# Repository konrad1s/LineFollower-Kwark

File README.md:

## Introduction

The LineFollower Robot is an autonomous robot designed to follow a predefined path marked by a black or white line.<br>
This project serves a quite advanced solution including hardware project, embedded software and PC QT application.

A short video demo is available on [YouTube](https://www.youtube.com/watch?v=Kh0NfI-lTgY).

Example - one of the first - linefollower run:

## Hardware
### **High level block diagram**

[![](https://mermaid.ink/img/pako:eNqVlW1vmzAQx7-K5ddJGiCEBE2T8tB2VWHJIM2kOVXlBjdBAxw59tb04bvPxk0ChLYaL8Bnfvf33dkcz3BJIwJduGJ4swaz4SJbZEBeW3Gvp0Y0TUUWLzGPaQZQybzVrLqGiSCcUr5GhxHwaSQS8gaRLDrRntK_hN2FYrNJdgDlFtBWQdmLp9S568yRGgCn1ZmDIeacsCIUcnwfJ_ETYdadNUdWy5qDOU04XhEQkJVIMKesRhQ0my9K8qXZ_FoReT9sf3QDkLwV9KKYkWVeIS84zk7CkWn7355QfgeT7TJOdCRq3ZF3rZed-ZZ54ZgmOow-qFlIsi2VRdttOUkB0mZtJGozD_XJsS0yzEdwPbsK2o5hhMV6nI_1SzW4PfFT4Q7Go3K4BWo_pbjL6dUkB5XUSR7nmTpwzEOD0G532nsbeOSB35aQoIoE8WpdYTy14A-BI4a5YKQuvr3ax2SlyGMW_yEA5Y9CNXwq9y6flAnMht2uYV58v9R0KYUKHJzCxWQOtIfyR61S8Pau6liq_fSnf3aofzHa_-SD-pyVi45iIvhG8KObV5_3-w7VFbQ2XmVEQ_sNrlahHgtOztmxC32RHjeDYFZ3OEoNSHKqb-gYRzefEKXv8H327NBd8pJ8IlrqrrABU8JSHEeyPz8rzwXka5KSBXTlMMLs9wIuslfJYcFpuMuW0OVMkAZkVKzW0H3AyVZaYhNhTsYxloc73SMbnP2itGhC9xk-QtexW72O_PC6_b7TdtqW0YA76Bq9luUYdsfoO92-2XOM1wZ8yv3brb7V6Rt2z7ZkV-nZpnQgUSw3y9e_lvwP8_oPiOn1SA?type=png)](https://mermaid.live/edit#pako:eNqVlW1vmzAQx7-K5ddJGiCEBE2T8tB2VWHJIM2kOVXlBjdBAxw59tb04bvPxk0ChLYaL8Bnfvf33dkcz3BJIwJduGJ4swaz4SJbZEBeW3Gvp0Y0TUUWLzGPaQZQybzVrLqGiSCcUr5GhxHwaSQS8gaRLDrRntK_hN2FYrNJdgDlFtBWQdmLp9S568yRGgCn1ZmDIeacsCIUcnwfJ_ETYdadNUdWy5qDOU04XhEQkJVIMKesRhQ0my9K8qXZ_FoReT9sf3QDkLwV9KKYkWVeIS84zk7CkWn7355QfgeT7TJOdCRq3ZF3rZed-ZZ54ZgmOow-qFlIsi2VRdttOUkB0mZtJGozD_XJsS0yzEdwPbsK2o5hhMV6nI_1SzW4PfFT4Q7Go3K4BWo_pbjL6dUkB5XUSR7nmTpwzEOD0G532nsbeOSB35aQoIoE8WpdYTy14A-BI4a5YKQuvr3ax2SlyGMW_yEA5Y9CNXwq9y6flAnMht2uYV58v9R0KYUKHJzCxWQOtIfyR61S8Pau6liq_fSnf3aofzHa_-SD-pyVi45iIvhG8KObV5_3-w7VFbQ2XmVEQ_sNrlahHgtOztmxC32RHjeDYFZ3OEoNSHKqb-gYRzefEKXv8H327NBd8pJ8IlrqrrABU8JSHEeyPz8rzwXka5KSBXTlMMLs9wIuslfJYcFpuMuW0OVMkAZkVKzW0H3AyVZaYhNhTsYxloc73SMbnP2itGhC9xk-QtexW72O_PC6_b7TdtqW0YA76Bq9luUYdsfoO92-2XOM1wZ8yv3brb7V6Rt2z7ZkV-nZpnQgUSw3y9e_lvwP8_oPiOn1SA)

### **Schematic and PCB**
Electronic circuit diagrams are available in the [Hardware/release/schematic](Hardware/release/schematic) folder.<br>
Gerbers files are available in the [Hardware/release/gerbers](Hardware/release/gerbers) folder.

**Main board:**

**Sensor board:**

**Encoder board:**

### **Component Details**
1. **STM32F722 MCU** <br>
ARM Cortex M7 microcontroller operating at the 216MHz with FPU, Cache, ITCM, DTCM. It powerful enough to handle algorithms and real-time processing required in linefollower applications.
3. **12x KTIR0711S** <br>
Phototransistor-based infrared sensors used to detect the line by measuring reflected IR light. Arranged in a array at the front of the robot to detect the position of the line. Outputs are connected to the MCU's ADC channels for monitoring.
4. **12x LEDs** <br>
Each LED corresponds to a KTIR0711S sensor, turned on when the sensor detects the line.
5. **2x AMS AS5040 Encoders** <br>
10-bit contactless magnetic rotary encoders providing precise angular position measurements. Thanks to the closed-loop control, encoders enables precise control of motor by providing feedback (velocity) for PID controllers.
6. **2x Pololu TB6612FNG Motor Driver Modules** <br>
H-bridge motor driver modules capable of controlling DC motors. Controller channels are combined to obtain higher current capacity.
7. **2x Pololu Motor 10:1 HPCB 6V DC Motors** <br>
High-power micro metal gearmotors with a 10:1 gear ratio
8. **Bluetooth Module JDY-31** <br>
Bluetooth serial module enables wireless communication between the robot and PC application.
9. **Power Supply Components** <br>
LiPo 7.4V battery used due to high energy density and ability to deliver powerful burst of current.<br>
3.3V Low dropout voltage regulator - steps down the battery voltage for MCU, sensors and others modules.

## Software

### **Main run loop**

The core functionality is implemented through an event-driven state machine. The primary signal is the LF_SIG_ADC_DATA_UPDATED, which is raised whenever new ADC data is available. Currently every 5ms, however increasing this frequency can lead to better control results.

The activity diagram presents simplified main robot algorithm in RUN state:

### **Code Structure**

Short brief about implemented software components:

- **linefollower:**
The core component of the software, manages the main event driven state machine. It handles the initialization of all subsystems. This component integrates sensor data processing, PID control algorithms, encoder feedback, and motor management. Additionally, it facilitates communication with the PC application for debugging and configuration purposes.
- **linefollower_config:**
Defines the default configurations and settings for the robot. This ensures that all hardware related configurations is easily adjustable.
- **lf_signal_queue:**
Implements a signal queue used for managing events and signals within the state machine.
- **linefollower_commands:**
Handles the processing of serial communication protocol (SCP) commands received from the PC application. It defines a set of commands for controlling the robot's modes, resetting the MCU, initiating calibration, reading and writing NVM data, toggling debug mode, retrieving session information, and entering the bootloader for firmware updates.
- **lf_calibrate:**
Manages the calibration process for the sensors. It handles the collection of sensor data during calibration runs, computes appropriate threshold values based on the collected values.
- **sensors:**
The module is responsible for interfacing with the robot's sensors to detect the line. It processes ADC data to determine states and manages the associated LEDs. Also implements algorithms to detect specific straight lines and right angles.
- **pid:**
Implements the PID control algorithms used to regulate the robot's motor speeds based on sensor and encoder feedback.
- **encoder:**
Manages the interfacing with the motor encoders to track the robot's velocity.
- **tb6612_motor:**
The module interfaces with the TB6612 motor driver hardware to control the robot's motors.
- **nvm:**
The module handles non-volatile memory operations, enabling the storage and retrieval of configuration data, calibration settings, and runtime parameters. The module ensures data integrity through CRC verification. The nvm module allows the robot to retain configurations across power cycles.
- **scp:**
Implements the Serial Communication Protocol (SCP) used for communication between the robot and external interfaces such as the PC application.
- **scp_dispatcher:**
The module acts as a handler for processing SCP commands received via the scp module. It manages a global command queue using a circular buffer to store incoming data, parses SCP packets, verifies data integrity using CRC, and dispatches valid commands to their respective handlers.

## Bootloader
Implemented bootloader allows for over the air firmware updates without the need of programmer. This is particularly useful for making quick updates "on the road." The bootloader uses the implemented SCP (Serial Communication Protocol) to receive firmware updates over Bluetooth.

There are 2 methods to enter the Bootloader:
1. **Command-Based Entry From Application** <br>
Send a specific command to trigger reset to the bootloader.
2. **Backdoor Entry** <br>
Enter the bootloader upon power-up by sending a specific command. Ensures that firmware updates are always possible, even if the application has errors causing continuous resets.

FLASH memory layout:

## **QT Application**

The QT Application provides a graphical interface to control, configure, and monitor the robot. The main sections of the interface and their functionalities are as follows:
1. **Connection Panel** <br>
Connection indicator and buttons to establish or terminate Bluetooth communication.
2. **Control Panel**<br>
Starting, stopping, resetting, and calibrating the robot, along with options to enable debug mode, read/write NVM, and display real-time data (speed, error, and timing metrics).
3. **Sensors Panel**<br>
Real-time sensor data display showing actual values, calibration references, and sensor weights.
4. **Configuration**<br>
Includes settings for general parameters, PID tuning for motor control, and encoder adjustments.
5. **Graph**<br>
A real-time graph displaying motor speeds, speed reduction, sensors error, enabling data analysis and adjustments for optimal performance.
6. **Bootloader**<br>
Firmware update controls, including options to enter bootloader mode, switch to the main application and flash new firmware via Bluetooth.
7. **Logs**<br>
Real-time log display with options to save or clear logs, providing detailed event tracking for debugging.

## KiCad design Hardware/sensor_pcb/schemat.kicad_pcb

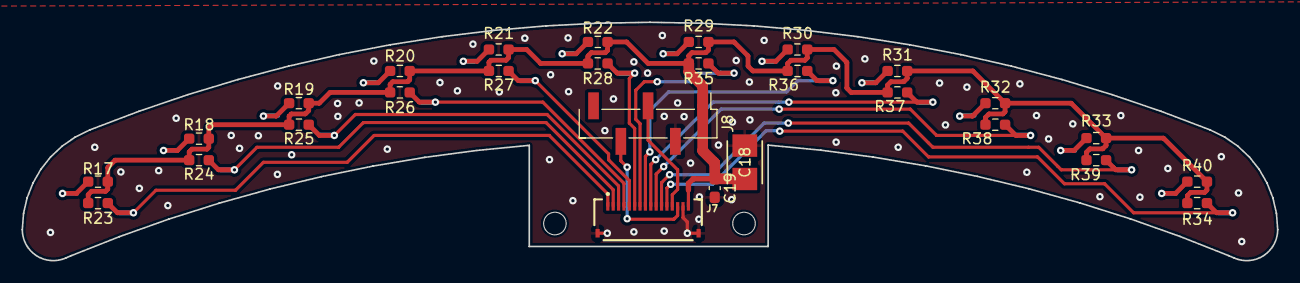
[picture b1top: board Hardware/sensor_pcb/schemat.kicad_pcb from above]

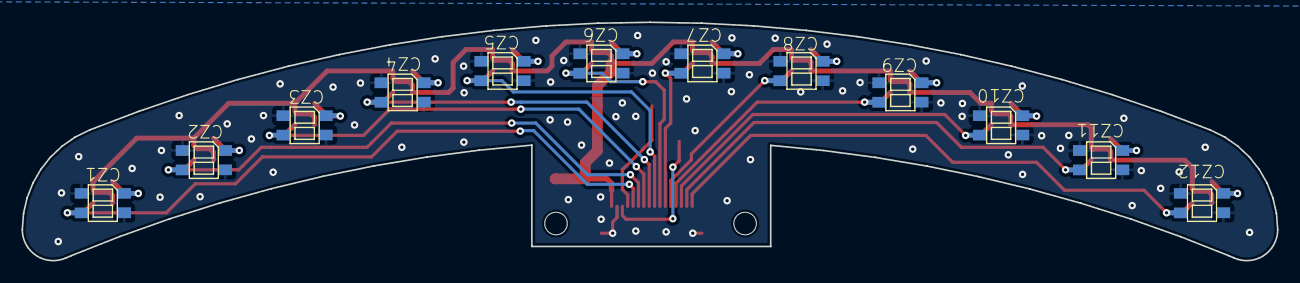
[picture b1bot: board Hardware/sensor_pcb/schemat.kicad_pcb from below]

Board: 2 copper layers, 116.8 x 22.2 mm, 42 parts (12 on the bottom side), 28 nets.

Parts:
@HOLE8, @HOLE9: (no value)
C18: 10uF; CAP_293D-B_VSS
C19: 100nF; C_0603_1608Metric_Pad1.08x0.95mm_HandSolder
CZ1, CZ2, CZ3, CZ4, CZ5, CZ6, CZ7, CZ8, CZ9, CZ10, CZ11, CZ12: KTIR0711S; TOP
J7: SENSOR_CONN; GCT_FFC2B28-16-G
J8: ToF Sensor; PinHeader_1x05_P2.54mm_Vertical_SMD_Pin1Left
R17, R18, R19, R20, R21, R22, R29, R30, R31, R32, R33, R34: 120; R_0603_1608Metric_Pad0.98x0.95mm_HandSolder
R23, R24, R25, R26, R27, R28, R35, R36, R37, R38, R39, R40: 20k; R_0603_1608Metric_Pad0.98x0.95mm_HandSolder

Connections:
+3.3V: C18.1, C19.1, J7.16, J8.1, R17.1, R18.1, R19.1, R20.1, R21.1, R22.1, R23.1, R24.1, R25.1, R26.1, R27.1, R28.1, R29.1, R30.1, R31.1, R32.1, R33.1, R34.1, R35.1, R36.1, R37.1, R38.1, R39.1, R40.1
/schemat_2/I2C_SCL: J7.13, J8.3
/schemat_2/I2C_SDA: J7.14, J8.4
/schemat_2/SENSOR1: CZ12.KOLEKTOR, J7.1, R23.2
/schemat_2/SENSOR2: CZ11.KOLEKTOR, J7.2, R24.2
/schemat_2/SENSOR3: CZ10.KOLEKTOR, J7.3, R25.2
/schemat_2/SENSOR4: CZ9.KOLEKTOR, J7.4, R26.2
/schemat_2/SENSOR5: CZ8.KOLEKTOR, J7.5, R27.2
/schemat_2/SENSOR6: CZ7.KOLEKTOR, J7.6, R28.2
/schemat_2/SENSOR7: CZ6.KOLEKTOR, J7.7, R35.2
/schemat_2/SENSOR8: CZ5.KOLEKTOR, J7.8, R36.2
/schemat_2/SENSOR9: CZ4.KOLEKTOR, J7.9, R37.2
/schemat_2/SENSOR10: CZ3.KOLEKTOR, J7.10, R38.2
/schemat_2/SENSOR11: CZ2.KOLEKTOR, J7.11, R39.2
/schemat_2/SENSOR12: CZ1.KOLEKTOR, J7.12, R40.2
GND: C18.2, C19.2, CZ1.EMITER, CZ1.KATODA, CZ2.EMITER, CZ2.KATODA, CZ3.EMITER, CZ3.KATODA, CZ4.EMITER, CZ4.KATODA, CZ5.EMITER, CZ5.KATODA, CZ6.EMITER, CZ6.KATODA, CZ7.EMITER, CZ7.KATODA, CZ8.EMITER, CZ8.KATODA, CZ9.EMITER, CZ9.KATODA, CZ10.EMITER, CZ10.KATODA, CZ11.EMITER, CZ11.KATODA, CZ12.EMITER, CZ12.KATODA, J7.15, J7.S1 (SHIELD), J7.S2 (SHIELD), J8.2
unnamed: CZ1.ANODA, R34.2
unnamed: CZ2.ANODA, R33.2
unnamed: CZ3.ANODA, R32.2
unnamed: CZ4.ANODA, R31.2
unnamed: CZ5.ANODA, R30.2
unnamed: CZ6.ANODA, R29.2
unnamed: CZ7.ANODA, R22.2
unnamed: CZ8.ANODA, R21.2
unnamed: CZ9.ANODA, R20.2
unnamed: CZ10.ANODA, R19.2
unnamed: CZ11.ANODA, R18.2
unnamed: CZ12.ANODA, R17.2

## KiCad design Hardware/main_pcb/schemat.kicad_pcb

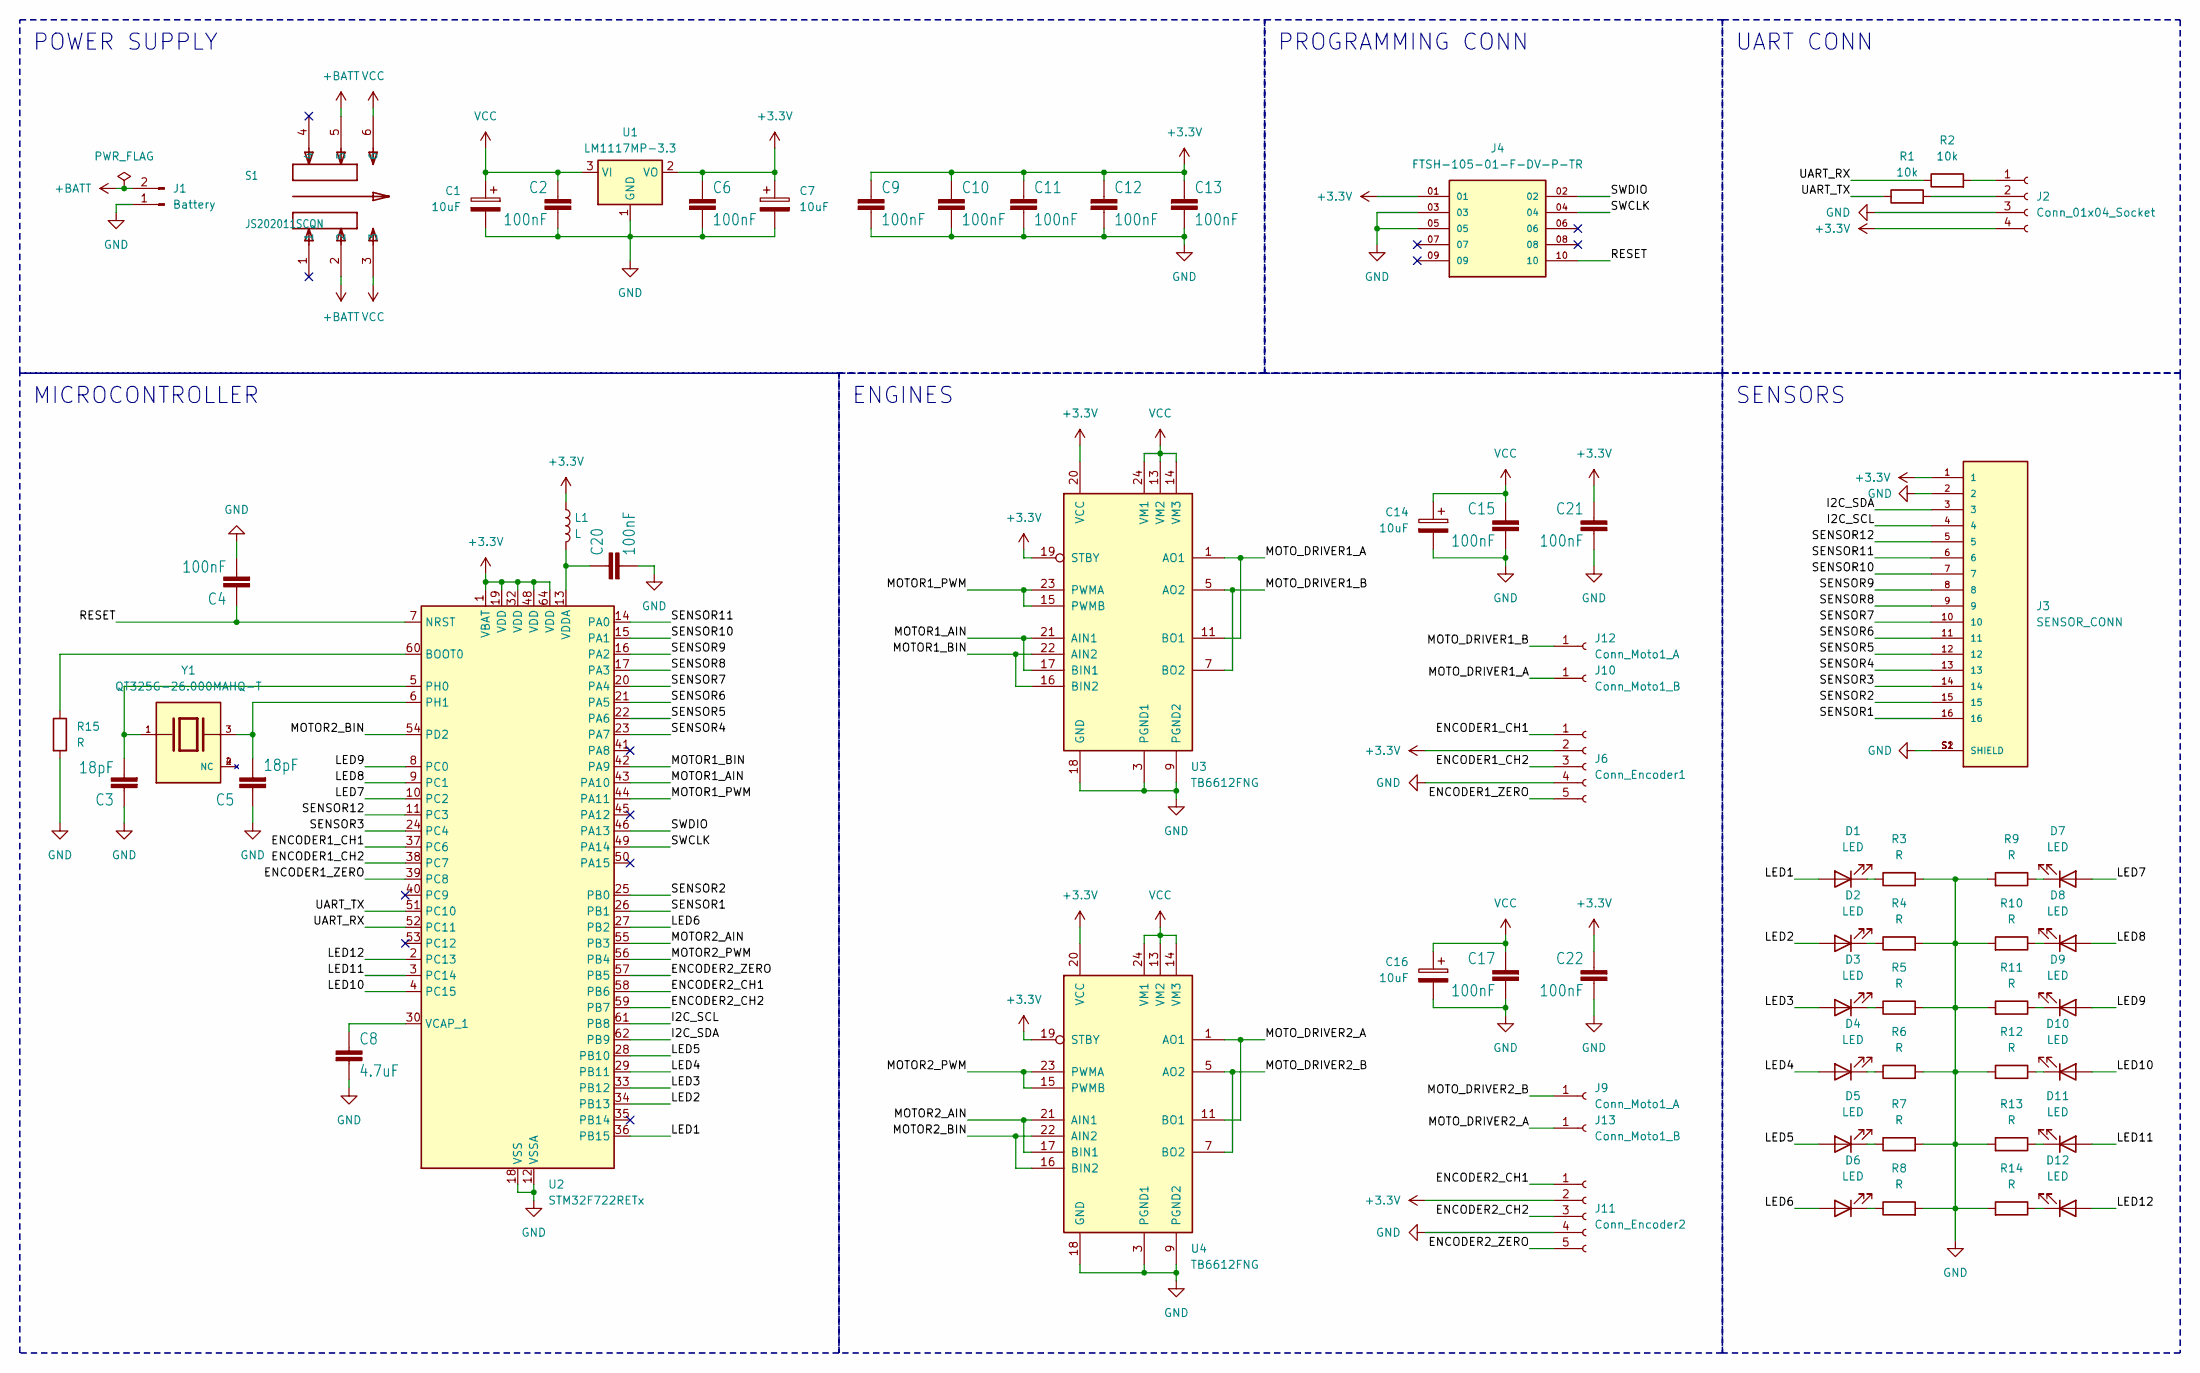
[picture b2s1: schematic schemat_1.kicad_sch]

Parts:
C1, C7, C14, C16: 10uF; CAP_293D-B_VSS
C2, C4, C6, C9, C10, C11, C12, C13, C15, C17, C20, C21, C22: 100nF; C_0603_1608Metric_Pad1.08x0.95mm_HandSolder
C3, C5: 18pF; C_0603_1608Metric_Pad1.08x0.95mm_HandSolder
C8: 4.7uF; C_0603_1608Metric_Pad1.08x0.95mm_HandSolder
D1, D2, D3, D4, D5, D6, D7, D8, D9, D10, D11, D12: LED; LED_0603_1608Metric_Pad1.05x0.95mm_HandSolder
J1: Battery; PinSocket_1x02_P2.54mm_Vertical
J2: Conn_01x04_Socket; PinSocket_1x04_P2.54mm_Vertical
J3: SENSOR_CONN; GCT_FFC2B28-16-G; PARTREV A
J4: FTSH-105-01-F-DV-P-TR; SAMTEC_FTSH-105-01-F-DV-P-TR; PARTREV R
J6: Conn_Encoder1; PinHeader_2x03_P2.54mm_Vertical_SMD
J9, J12: Conn_Moto1_A; PinHeader_1x01_P2.54mm_Vertical
J10, J13: Conn_Moto1_B; PinHeader_1x01_P2.54mm_Vertical
J11: Conn_Encoder2; PinHeader_2x03_P2.54mm_Vertical_SMD
L1: L; L_0603_1608Metric_Pad1.05x0.95mm_HandSolder
R1, R2: 10k; R_0603_1608Metric_Pad0.98x0.95mm_HandSolder
R3, R4, R5, R6, R7, R8, R9, R10, R11, R12, R13, R14, R15: R; R_0603_1608Metric_Pad0.98x0.95mm_HandSolder
S1: JS202011SCQN; SW_JS202011SCQN
U1: LM1117MP-3.3; SOT-223-3_TabPin2
U2: STM32F722RETx; LQFP-64_10x10mm_P0.5mm
U3, U4: TB6612FNG; SSOP-24_5.3x8.2mm_P0.65mm
Y1: QT325G-26.000MAHQ-T; XTAL_QT325G-26.000MAHQ-T; PARTREV N/A

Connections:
+3.3V: C6.1, C7.1, C9.1, C10.1, C11.1, C12.1, C13.1, C21.1, C22.1, J2.4, J3.1, J4.01, J6.2, J11.2, L1.1, U1.2 (VO), U2.1 (VBAT), U2.19 (VDD), U2.32 (VDD), U2.48 (VDD), U2.64 (VDD), U3.19 (STBY), U3.20 (VCC), U4.19 (STBY), U4.20 (VCC)
+BATT: J1.2, S1.2, S1.5
/schemat_1/ENCODER1_CH1: J6.1, U2.37 (PC6)
/schemat_1/ENCODER1_CH2: J6.3, U2.38 (PC7)
/schemat_1/ENCODER1_ZERO: J6.5, U2.39 (PC8)
/schemat_1/ENCODER2_CH1: J11.1, U2.58 (PB6)
/schemat_1/ENCODER2_CH2: J11.3, U2.59 (PB7)
/schemat_1/ENCODER2_ZERO: J11.5, U2.57 (PB5)
/schemat_1/I2C_SCL: J3.4, U2.61 (PB8)
/schemat_1/I2C_SDA: J3.3, U2.62 (PB9)
/schemat_1/LED1: D1.2 (A), U2.36 (PB15)
/schemat_1/LED2: D2.2 (A), U2.34 (PB13)
/schemat_1/LED3: D3.2 (A), U2.33 (PB12)
/schemat_1/LED4: D4.2 (A), U2.29 (PB11)
/schemat_1/LED5: D5.2 (A), U2.28 (PB10)
/schemat_1/LED6: D6.2 (A), U2.27 (PB2)
/schemat_1/LED7: D7.2 (A), U2.10 (PC2)
/schemat_1/LED8: D8.2 (A), U2.9 (PC1)
/schemat_1/LED9: D9.2 (A), U2.8 (PC0)
/schemat_1/LED10: D10.2 (A), U2.4 (PC15)
/schemat_1/LED11: D11.2 (A), U2.3 (PC14)
/schemat_1/LED12: D12.2 (A), U2.2 (PC13)
/schemat_1/MOTOR1_AIN: U2.43 (PA10), U3.17 (BIN1), U3.21 (AIN1)
/schemat_1/MOTOR1_BIN: U2.42 (PA9), U3.16 (BIN2), U3.22 (AIN2)
/schemat_1/MOTOR1_PWM: U2.44 (PA11), U3.15 (PWMB), U3.23 (PWMA)
/schemat_1/MOTOR2_AIN: U2.55 (PB3), U4.17 (BIN1), U4.21 (AIN1)
/schemat_1/MOTOR2_BIN: U2.54 (PD2), U4.16 (BIN2), U4.22 (AIN2)
/schemat_1/MOTOR2_PWM: U2.56 (PB4), U4.15 (PWMB), U4.23 (PWMA)
/schemat_1/MOTO_DRIVER1_A: J10.1, U3.1 (AO1), U3.2 (AO1), U3.11 (BO1), U3.12 (BO1)
/schemat_1/MOTO_DRIVER1_B: J12.1, U3.5 (AO2), U3.6 (AO2), U3.7 (BO2), U3.8 (BO2)
/schemat_1/MOTO_DRIVER2_A: J13.1, U4.1 (AO1), U4.2 (AO1), U4.11 (BO1), U4.12 (BO1)
/schemat_1/MOTO_DRIVER2_B: J9.1, U4.5 (AO2), U4.6 (AO2), U4.7 (BO2), U4.8 (BO2)
/schemat_1/RESET: C4.1, J4.10, U2.7 (NRST)
/schemat_1/SENSOR1: J3.16, U2.26 (PB1)
/schemat_1/SENSOR2: J3.15, U2.25 (PB0)
/schemat_1/SENSOR3: J3.14, U2.24 (PC4)
/schemat_1/SENSOR4: J3.13, U2.23 (PA7)
/schemat_1/SENSOR5: J3.12, U2.22 (PA6)
/schemat_1/SENSOR6: J3.11, U2.21 (PA5)
/schemat_1/SENSOR7: J3.10, U2.20 (PA4)
/schemat_1/SENSOR8: J3.9, U2.17 (PA3)
/schemat_1/SENSOR9: J3.8, U2.16 (PA2)
/schemat_1/SENSOR10: J3.7, U2.15 (PA1)
/schemat_1/SENSOR11: J3.6, U2.14 (PA0)
/schemat_1/SENSOR12: J3.5, U2.11 (PC3)
/schemat_1/SWCLK: J4.04, U2.49 (PA14)
/schemat_1/SWDIO: J4.02, U2.46 (PA13)
/schemat_1/UART_RX: R2.1, U2.52 (PC11)
/schemat_1/UART_TX: R1.1, U2.51 (PC10)
GND: C1.2, C2.2, C3.1, C4.2, C5.1, C6.2, C7.2, C8.2, C9.2, C10.2, C11.2, C12.2, C13.2, C14.2, C15.2, C16.2, C17.2, C20.2, C21.2, C22.2, J1.1, J2.3, J3.2, J3.S1 (SHIELD), J3.S2 (SHIELD), J4.03, J4.05, J6.4, J11.4, R3.2, R4.2, R5.2, R6.2, R7.2, R8.2, R9.2, R10.2, R11.2, R12.2, R13.2, R14.2, R15.2, U1.1 (GND), U2.12 (VSSA), U2.18 (VSS), U2.31 (VSS), U2.47 (VSS), U2.63 (VSS), U3.3 (PGND1), U3.4 (PGND1), U3.9 (PGND2), U3.10 (PGND2), U3.18 (GND), U4.3 (PGND1), U4.4 (PGND1), U4.9 (PGND2), U4.10 (PGND2), U4.18 (GND)
unnamed: D1.1 (K), R3.1
unnamed: D2.1 (K), R4.1
unnamed: D3.1 (K), R5.1
unnamed: D4.1 (K), R6.1
unnamed: D5.1 (K), R7.1
unnamed: D6.1 (K), R8.1
unnamed: D7.1 (K), R9.1
unnamed: D8.1 (K), R10.1
unnamed: D9.1 (K), R11.1
unnamed: D10.1 (K), R12.1
unnamed: D11.1 (K), R13.1
unnamed: D12.1 (K), R14.1
unnamed: J2.1, R2.2
unnamed: J2.2, R1.2
unnamed: R15.1, U2.60 (BOOT0)
unnamed: C3.2, U2.5 (PH0), Y1.1
unnamed: C5.2, U2.6 (PH1), Y1.3
unnamed: C8.1, U2.30 (VCAP_1)
unnamed: C20.1, L1.2, U2.13 (VDDA)
VCC: C1.1, C2.1, C14.1, C15.1, C16.1, C17.1, S1.3, S1.6, U1.3 (VI), U3.13 (VM2), U3.14 (VM3), U3.24 (VM1), U4.13 (VM2), U4.14 (VM3), U4.24 (VM1)

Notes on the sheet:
UART CONN
ENGINES
PROGRAMMING CONN
POWER SUPPLY
SENSORS
MICROCONTROLLER

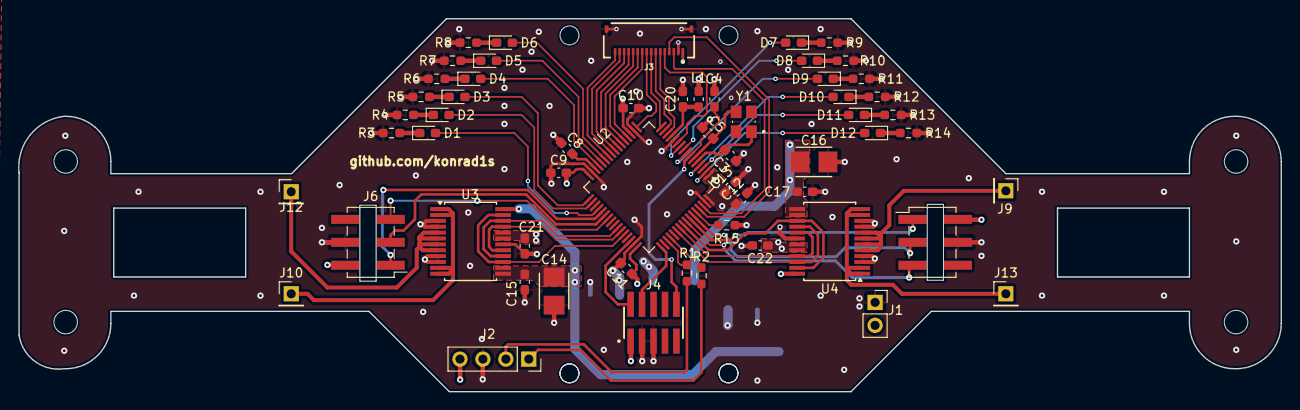
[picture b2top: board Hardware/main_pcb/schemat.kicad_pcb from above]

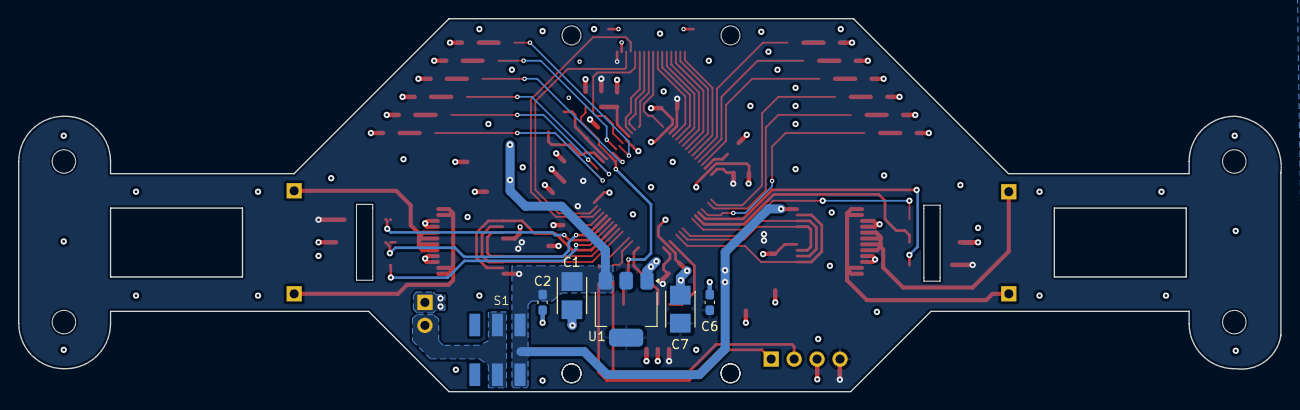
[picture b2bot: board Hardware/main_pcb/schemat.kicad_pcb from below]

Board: 4 copper layers, 139.7 x 41.3 mm, 72 parts (6 on the bottom side), 70 nets.

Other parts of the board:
@HOLE0, @HOLE1, @HOLE2, @HOLE3, @HOLE8, @HOLE8#2, @HOLE9, @HOLE9#2: (no value)

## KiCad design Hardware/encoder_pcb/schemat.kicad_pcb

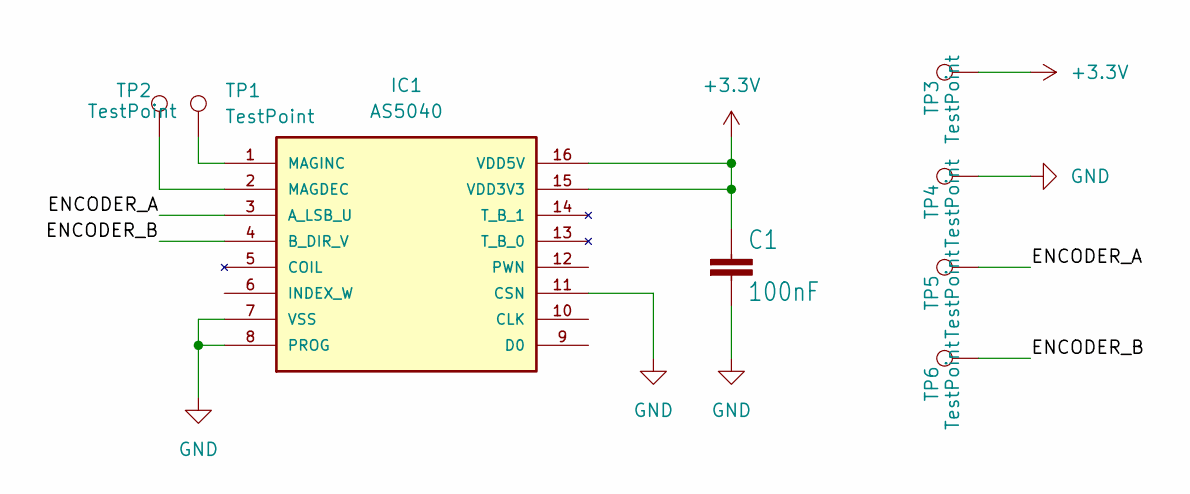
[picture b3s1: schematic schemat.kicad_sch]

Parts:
C1: 100nF; C_0603_1608Metric_Pad1.08x0.95mm_HandSolder
IC1: AS5040; SSOP16
TP1, TP2: TestPoint; TestPoint_THTPad_1.0x1.0mm_Drill0.5mm
TP3, TP4, TP5, TP6: TestPoint; SolderWirePad_1x01_SMD_1x2mm

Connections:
+3.3V: C1.1, IC1.15 (VDD3V3), IC1.16 (VDD5V), TP3.1
/ENCODER_A: IC1.3 (A_LSB_U), TP5.1
/ENCODER_B: IC1.4 (B_DIR_V), TP6.1
GND: C1.2, IC1.7 (VSS), IC1.8 (PROG), IC1.11 (CSN), TP4.1
unnamed: IC1.2 (MAGDEC), TP2.1
unnamed: IC1.1 (MAGINC), TP1.1

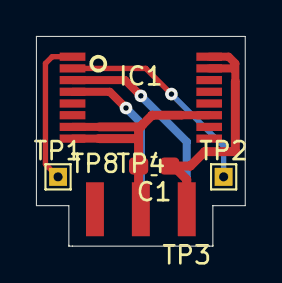
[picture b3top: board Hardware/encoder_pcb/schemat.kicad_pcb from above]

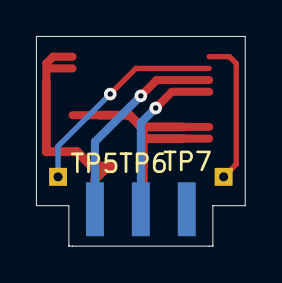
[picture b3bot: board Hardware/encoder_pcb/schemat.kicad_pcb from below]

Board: 2 copper layers, 11.6 x 11.6 mm, 10 parts (3 on the bottom side), 6 nets.

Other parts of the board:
TP7, TP8: TestPoint; SolderWirePad_1x01_SMD_1x2mm

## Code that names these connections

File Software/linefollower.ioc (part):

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Mcu.Name=STM32F722R(C-E)Tx
Mcu.Package=LQFP64
Mcu.UserName=STM32F722RETx
PA0-WKUP.GPIOParameters=GPIO_Label
PA0-WKUP.GPIO_Label=SENSOR11
PA0-WKUP.Signal=ADCx_IN0
PA1.GPIOParameters=GPIO_Label
PA1.GPIO_Label=SENSOR10
PA1.Signal=ADCx_IN1
PA10.GPIOParameters=GPIO_Label
PA10.GPIO_Label=MOTOR1_AIN
PA10.Signal=GPIO_Output
PA11.GPIOParameters=GPIO_Label
PA11.GPIO_Label=MOTOR1_PWM
PA11.Signal=S_TIM1_CH4
PA13.Mode=Serial_Wire
PA13.Signal=SYS_JTMS-SWDIO
PA14.Mode=Serial_Wire
PA14.Signal=SYS_JTCK-SWCLK
PA2.GPIOParameters=GPIO_Label
PA2.GPIO_Label=SENSOR9
PA2.Signal=ADCx_IN2
PA3.GPIOParameters=GPIO_Label
PA3.GPIO_Label=SENSOR8
PA3.Signal=ADCx_IN3
PA4.GPIOParameters=GPIO_Label
PA4.GPIO_Label=SENSOR7
PA4.Signal=ADCx_IN4
PA5.GPIOParameters=GPIO_Label
PA5.GPIO_Label=SENSOR6
PA5.Signal=ADCx_IN5
PA6.GPIOParameters=GPIO_Label
PA6.GPIO_Label=SENSOR5
PA6.Signal=ADCx_IN6
PA7.GPIOParameters=GPIO_Label
PA7.GPIO_Label=SENSOR4
PA7.Signal=ADCx_IN7
PA8.Mode=I2C
PA8.Signal=I2C3_SCL
PA9.GPIOParameters=GPIO_Label
PA9.GPIO_Label=MOTOR1_BIN
PA9.Signal=GPIO_Output
PB0.GPIOParameters=GPIO_Label
PB0.GPIO_Label=SENSOR2
PB0.Signal=ADCx_IN8
PB1.GPIOParameters=GPIO_Label
PB1.GPIO_Label=SENSOR1
PB1.Signal=ADCx_IN9
PB10.GPIOParameters=GPIO_Label
PB10.GPIO_Label=LED5
PB10.Signal=GPIO_Output
PB11.GPIOParameters=GPIO_Label
PB11.GPIO_Label=LED4
PB11.Signal=GPIO_Output
PB12.GPIOParameters=GPIO_Label
PB12.GPIO_Label=LED3
PB12.Signal=GPIO_Output
PB13.GPIOParameters=GPIO_Label
PB13.GPIO_Label=LED2
PB13.Signal=GPIO_Output
PB15.GPIOParameters=GPIO_Label
PB15.GPIO_Label=LED1
PB15.Signal=GPIO_Output
PB2.GPIOParameters=GPIO_Label
PB2.GPIO_Label=LED6
PB2.Signal=GPIO_Output
PB3.GPIOParameters=GPIO_Label
PB3.GPIO_Label=MOTOR2_AIN
PB3.Signal=GPIO_Output
PB4.GPIOParameters=GPIO_Label
PB4.GPIO_Label=MOTOR2_PWM
PB4.Signal=S_TIM3_CH1
PB6.GPIOParameters=GPIO_Label
PB6.GPIO_Label=ENCODER_CH1
PB6.Signal=S_TIM4_CH1
PB7.GPIOParameters=GPIO_Label
PB7.GPIO_Label=ENCODER_CH2
PB7.Signal=S_TIM4_CH2
PB8.Mode=I2C
PB8.Signal=I2C1_SCL
PB9.Mode=I2C
PB9.Signal=I2C1_SDA
PC0.GPIOParameters=GPIO_Label
PC0.GPIO_Label=LED9
PC0.Signal=GPIO_Output
PC1.GPIOParameters=GPIO_Label
PC1.GPIO_Label=LED8
PC1.Signal=GPIO_Output
PC10.Mode=Asynchronous
PC10.Signal=UART4_TX
PC11.Mode=Asynchronous
PC11.Signal=UART4_RX
PC13.GPIOParameters=GPIO_Label
PC13.GPIO_Label=LED12
PC13.Signal=GPIO_Output
PC14-OSC32_IN.GPIOParameters=GPIO_Label
PC14-OSC32_IN.GPIO_Label=LED11
PC14-OSC32_IN.Signal=GPIO_Output
PC15-OSC32_OUT.GPIOParameters=GPIO_Label
PC15-OSC32_OUT.GPIO_Label=LED10
PC15-OSC32_OUT.Signal=GPIO_Output
PC2.GPIOParameters=GPIO_Label
PC2.GPIO_Label=LED7
PC2.Signal=GPIO_Output
PC3.GPIOParameters=GPIO_Label
PC3.GPIO_Label=SENSOR12
PC3.Signal=ADCx_IN13
PC4.GPIOParameters=GPIO_Label
PC4.GPIO_Label=SENSOR3
PC4.Signal=ADCx_IN14
PC6.GPIOParameters=GPIO_Label
PC6.GPIO_Label=ENCODER_CH1
PC6.Signal=S_TIM8_CH1
PC7.GPIOParameters=GPIO_Label
PC7.GPIO_Label=ENCODER_CH2
PC7.Signal=S_TIM8_CH2
PC9.Mode=I2C
PC9.Signal=I2C3_SDA
PD2.GPIOParameters=GPIO_Label
PD2.GPIO_Label=MOTOR2_BIN
PD2.Signal=GPIO_Output
PH0-OSC_IN.Mode=HSE-External-Oscillator
PH0-OSC_IN.Signal=RCC_OSC_IN
PH1-OSC_OUT.Mode=HSE-External-Oscillator
PH1-OSC_OUT.Signal=RCC_OSC_OUT
RCC.HSE_VALUE=25000000
RCC.SYSCLKFreq_VALUE=216000000
RCC.SYSCLKSource=RCC_SYSCLKSOURCE_PLLCLK
board=custom

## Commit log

2024-08-31 gitignore file added
2024-08-31 STM32 project added, pinout configured
2024-08-31 Added PCB layouts
2024-08-31 PID algorithm implemented
2024-09-01 Pid source files moved to Src/Inc directory
2024-09-01 Non volatile manager implemented
2024-09-02 Hardware CRC added
2024-09-02 Non volatile manager - CRC validation data added
2024-09-02 Perform write only if data has been changed (based on calculated CRC)
2024-09-02 Non volatile memory default data implemented
2024-09-02 UART with DMA enabled
2024-09-03 Serial Communication Protocol implemented
2024-09-04 SCP config structure added
2024-09-04 SCP Error Handler added
2024-09-04 ADC sensor channels configured in DMA mode
2024-09-04 LineFollower main file and config created
2024-09-05 Sensor component created
2024-09-07 Sensor error calculation implemented
2024-09-08 Serial Communication Protocol Dispatcher implemented
2024-09-08 Use one circular buffer for commands
2024-09-08 Command size check added
2024-09-08 SCP Transmit function implemented
2024-09-08 Some get/set commands implemented
2024-09-08 CPU frequency set to 216MHz
2024-09-08 Motor timer PWM frequency set to 36kHz
2024-09-08 NVM_Write refactored, moved flash write related functionality do separate function
2024-09-10 Fixed bug with invalid CRC stored in NVM
2024-09-10 Pololu TB6612FNG motor driver implemented
2024-09-10 Sensor refactored, created only one manager
2024-09-11 ADC timer trigger configured
2024-09-11 ADC conversion end callback added
2024-09-12 Sensors calibration implemented
2024-09-12 Initialization refactored
2024-09-12 Signal queue implemented
2024-09-12 Signal dispatcher implemented, refactor initialization, create linefollower main structure
2024-09-12 Data updated signal implemented
2024-09-12 Sensor calibration signal implemented
2024-09-13 Fixed motor driver pointer bug
2024-09-13 Commands processing implemented, added some commands handling
2024-09-14 QT Application base project added, Bluetooth connection implemented
2024-09-14 Read, Write NvM commands added
2024-09-14 LedInidiactor plugin implemented
2024-09-14 UI design updated, added linefollower control and sensors sections
2024-09-15 QT: bluetoothHandler, Command, NvmLayout, PidSetting classes added and implemented
2024-09-15 QT UI Added nvm section
2024-09-15 Implemented constexpr size function for nvm and pid classes
2024-09-16 QT implemented wait timeout for response
2024-09-16 Nvm, Pid handling big and little endian
2024-09-16 QT: Gui filled with received nvm data
2024-09-16 QT: Added errors emit in bluetooth handler
2024-09-16 Connection status indicator added
2024-09-17 Sensor calibration threshold added into nvm
2024-09-19 Debug data implemented
2024-09-19 Nvm Write implemented
2024-09-24 PCB sensor layout updated
2024-09-25 QT: Added logging system
2024-09-25 QT: Bluetooth autoconnection implemented
2024-09-28 QT: Plot class implemented
2024-09-28 QT: GUI updated, added plot section
2024-09-28 SCP refactored, packet based communcation added
2024-09-29 QT: SCP packet based communcation implemented
2024-09-29 Fixed SCP data length receiving
2024-09-29 Debug data send triggered using timer (signal every 50ms)
2024-09-29 QT: Debug data plotting implemented
2024-09-29 CRC16 changed to lokuptable CCITT algotihm
2024-09-29 Missing critical sections added
2024-09-29 nvm, lf_signal, pid function briefs updated
2024-09-29 All compiler warnings fixed
2024-10-03 Encoder driver implemented
2024-10-04 Bootloader project added
2024-10-05 Bootloader: Scp resued from application
2024-10-05 Bootloader: Boot commands and event queue implemented
2024-10-05 Bootloader: Flash Manager implemented
2024-10-05 Bootloader: Draft state machine implemented
2024-10-05 QT: UI updated added bootloader section
2024-10-05 QT: Bootloader class implemented
2024-10-06 Bootloader: State tranisions from idle to flashing implemented
2024-10-08 Application relocated to the Sector 1, address 0x08004000
2024-10-12 Jumping to application implemented
2024-10-12 QT, Bootloader: Added application validation using crc32
2024-10-13 Fixed inverted led sensors configuration
2024-10-13 QT: Fixed led indicator update bug
2024-10-13 Nvm write added after sensor calibration
2024-10-13 Jumping between app and boot implemented, no_init section added
2024-10-13 Changed NvM Flash sectored used from 128Kb to 16Kb
2024-10-13 Get active session command implemented
2024-10-13 Added leds effect in bootloader
2024-10-13 Not needed commads deleted
2024-10-15 Target speed added to nvm, QT GUI Nvm updated
2024-10-16 Encoder integration with the main algorithm
2024-10-16 Added motor speeds to the debug data
2024-10-21 Minor fixes related to configuration, sensor error calculation
2024-10-26 Added timeout if no sensor detected line
2024-10-26 Motors velocity result in meters per second
2024-10-27 Fixed bug with reversed motor rotation, updated default nvm values
2024-10-27 Linefollower main state machine refactored
2024-10-28 Improved visual aspects of the code
2024-10-30 Sensors module refactored
2024-11-03 Encoder PID adjustment, Changed ADC measurements period from 20ms to 5ms
2024-11-04 Sesnsors right angle detection implemented
2024-11-08 Straight line and stabilize detection implemented
2024-11-10 Added timers mechanisms, implemented speed reduction when right angle is detected
2024-11-10 Calibration method uses the timers mechanism
2024-11-10 Measurements delta time calculation instead using const value
2024-11-10 QT: Added speed reduced to the motor chart, debug information improvements
2024-11-14 Minor fixes in schematics, added gerbers and schematics pdfs
2024-11-14 Update README.md - Added youtube link
2024-11-17 MIT License file added
2024-11-17 Bootloader: Functions briefs and code sections
2024-11-17 Missing filles added
2024-11-17 Readme images added: Flash memory layout, PCB layouts
